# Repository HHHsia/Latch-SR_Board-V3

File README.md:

# Latch-SR_Board-V3  
含200單元Shift Register、400單元Latch(可選擇為200x2、80x5、40x10 Latch矩陣)  
輸入輸出各為20組20 pin FPC排線

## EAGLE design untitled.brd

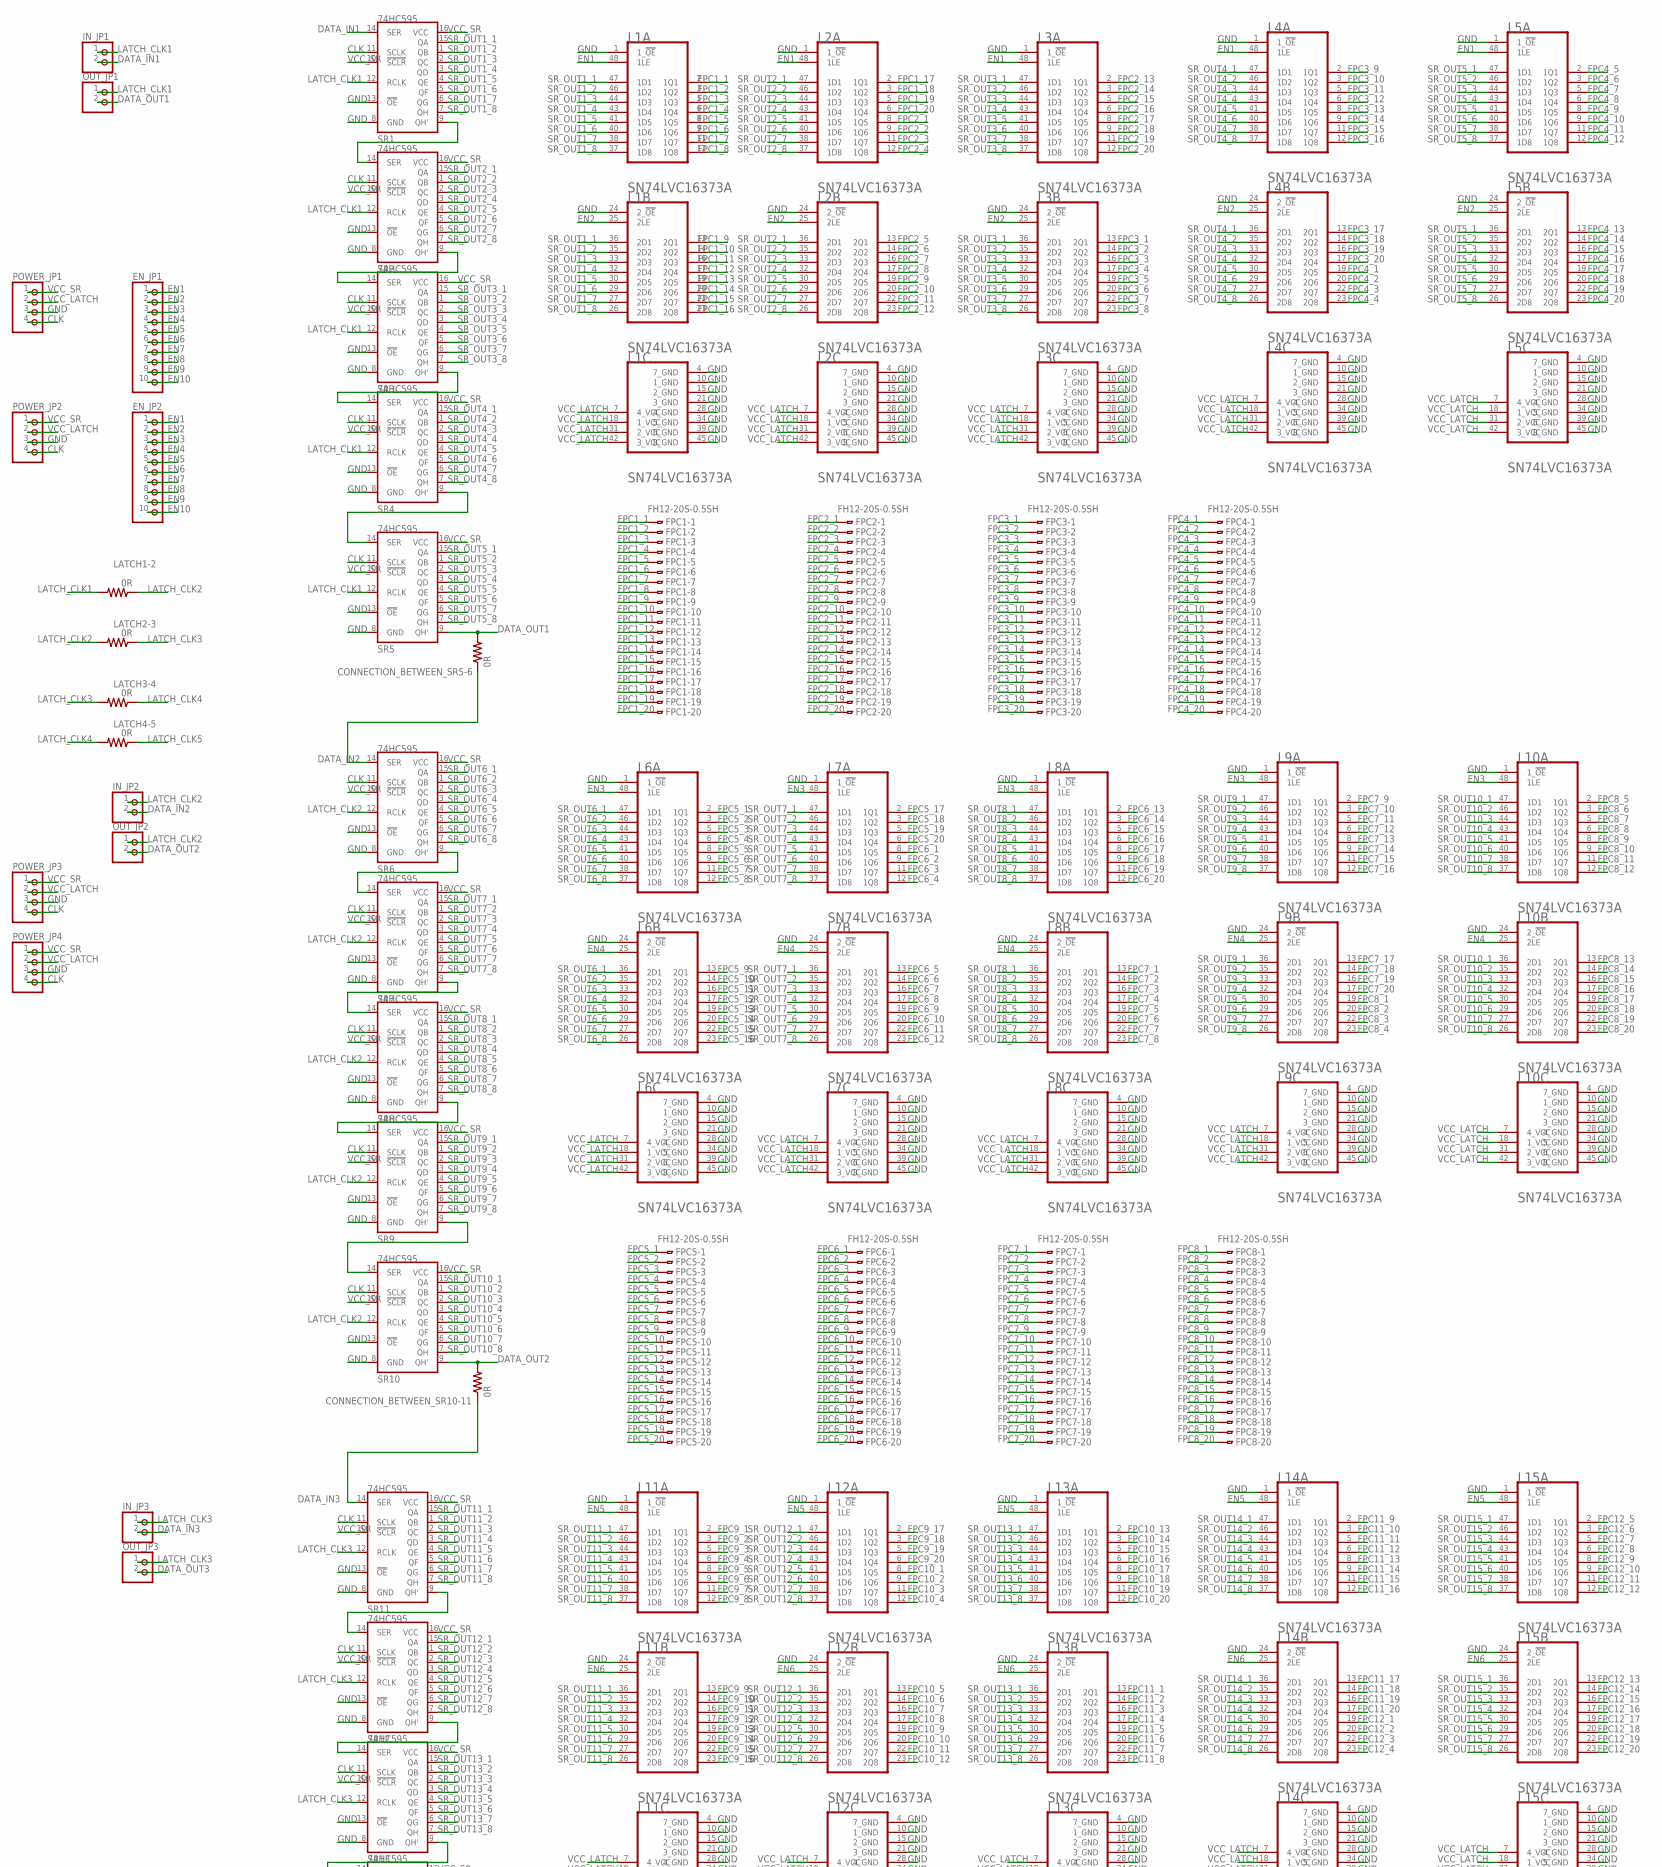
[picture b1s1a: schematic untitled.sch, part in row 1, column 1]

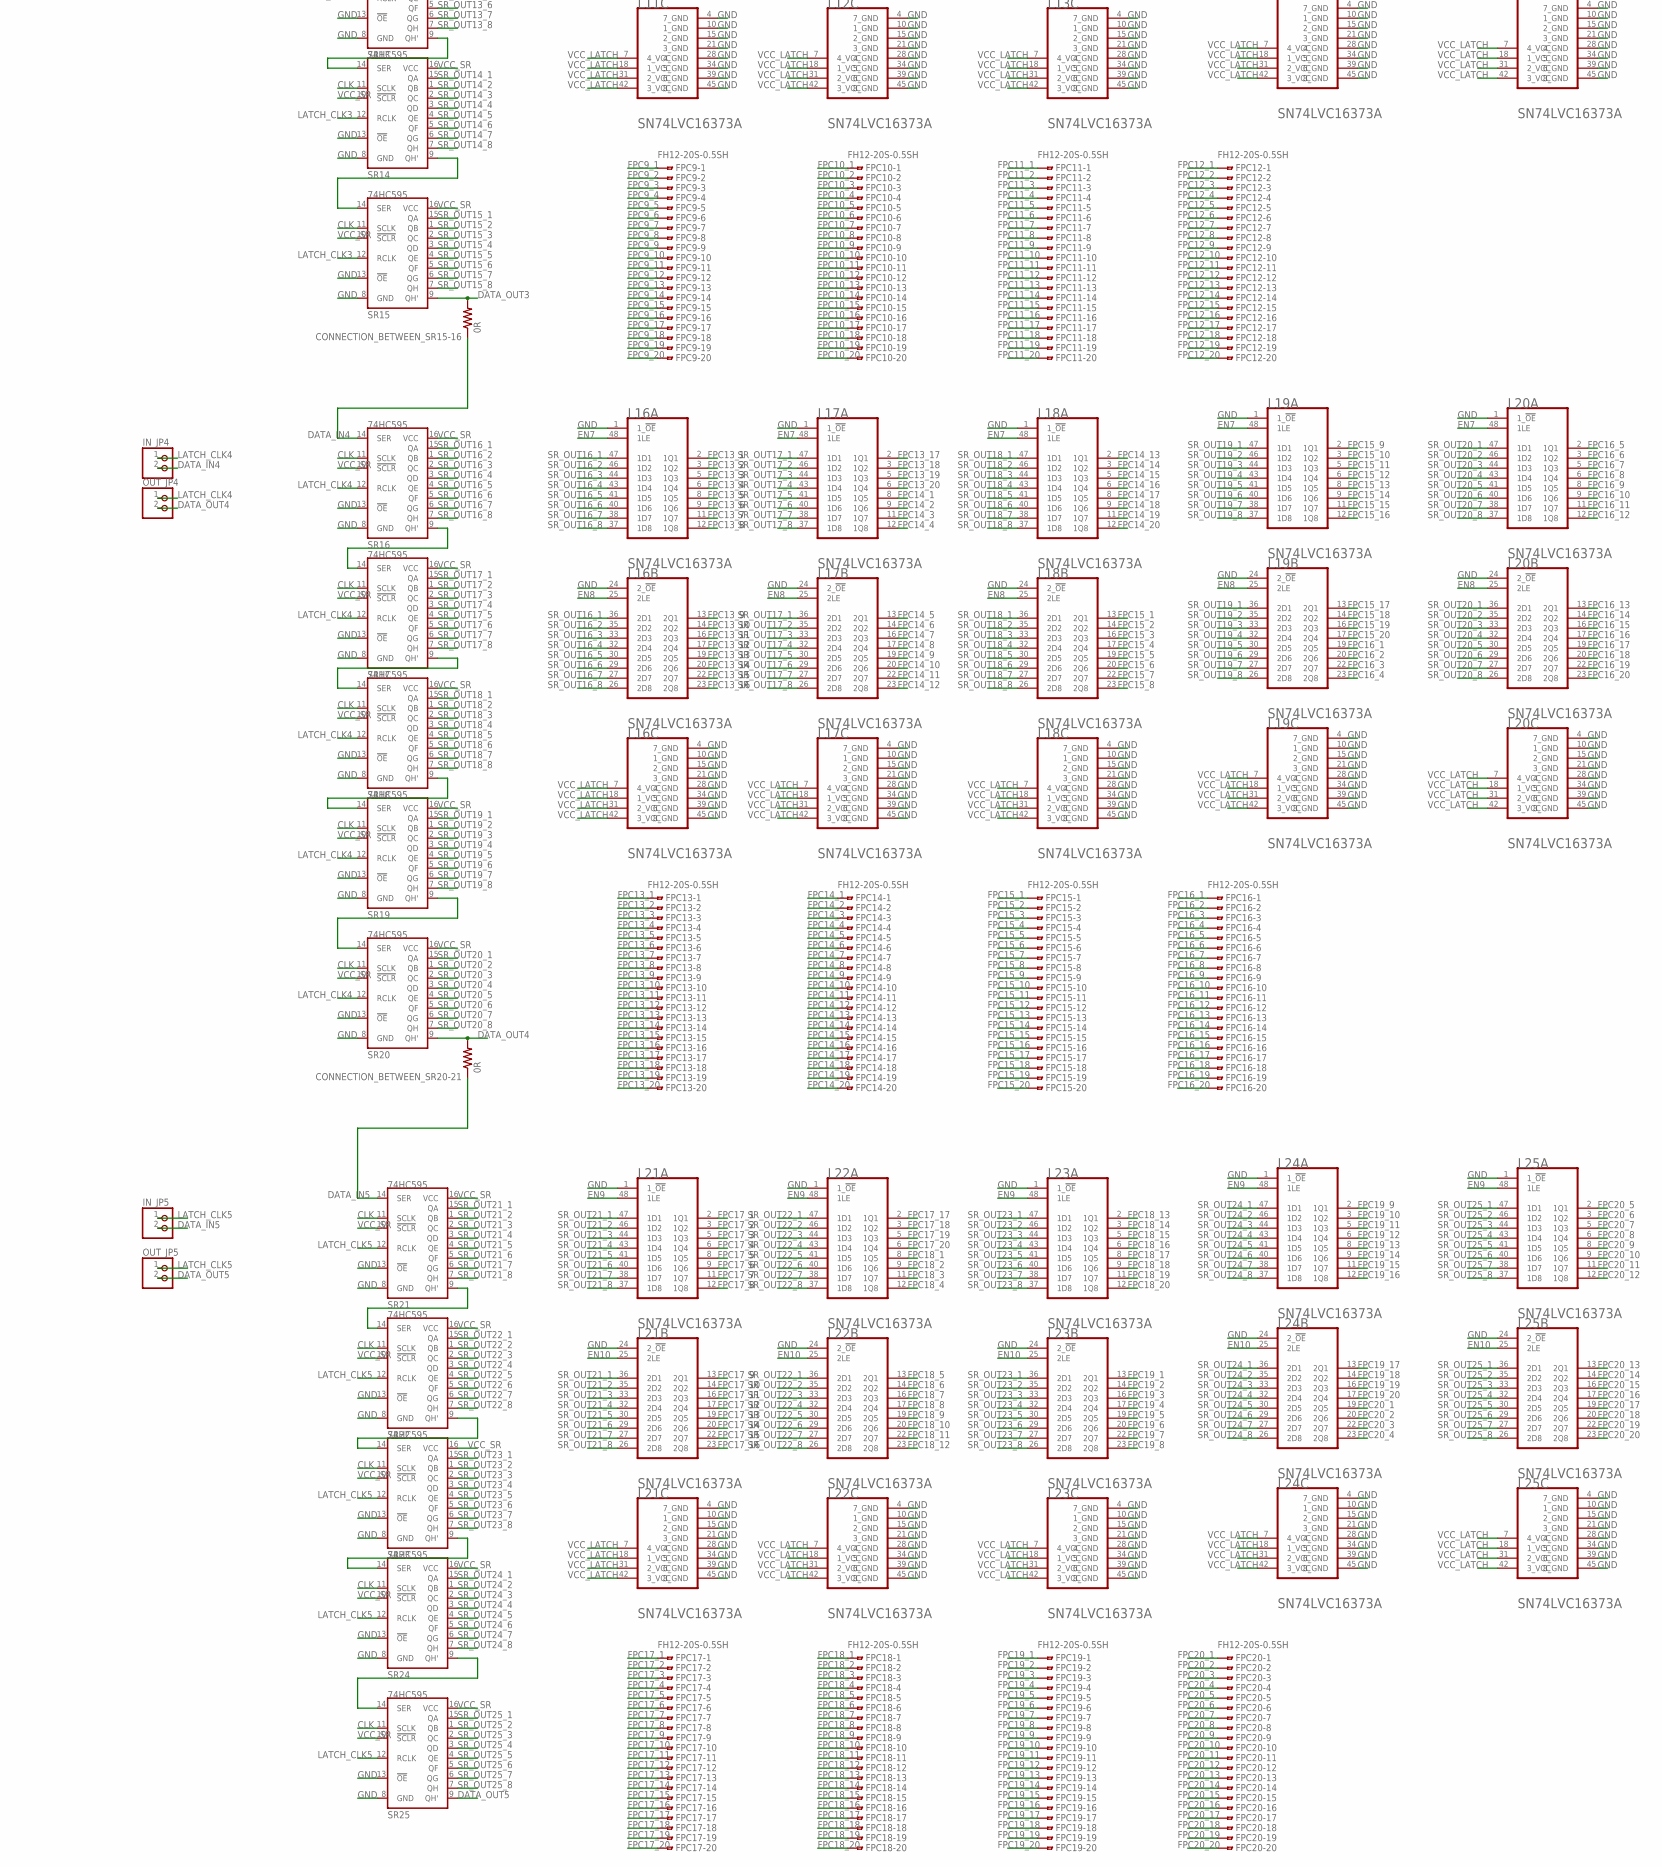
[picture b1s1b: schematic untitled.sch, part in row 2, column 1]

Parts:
CONNECTION_BETWEEN_SR5-6, CONNECTION_BETWEEN_SR10-11, CONNECTION_BETWEEN_SR15-16, CONNECTION_BETWEEN_SR20-21: 0R; M0805
EN_JP1, EN_JP2: PINHD-1X10; 1X10
FPC1, FPC2, FPC3, FPC4, FPC5, FPC6, FPC7, FPC8, FPC9, FPC10, FPC11, FPC12, FPC13, FPC14, FPC15, FPC16, FPC17, FPC18, FPC19, FPC20: FH12-20S-0.5SH
IN_JP1, IN_JP2, IN_JP3, IN_JP4, IN_JP5: PINHD-1X2; 1X02
L1, L2, L3, L4, L5, L6, L7, L8, L9, L10, L11, L12, L13, L14, L15, L16, L17, L18, L19, L20, L21, L22, L23, L24, L25: TEXAS_INSTRUMENTS_SN74LVC16373ATEXAS_INSTRUMENTS_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; TEXAS_INSTRUMENTS_SN74LVC16373A_2
LATCH1-2, LATCH2-3, LATCH3-4, LATCH4-5: 0R; M0805
OUT_JP1, OUT_JP2, OUT_JP3, OUT_JP4, OUT_JP5: PINHD-1X2; 1X02
POWER_JP1, POWER_JP2, POWER_JP3, POWER_JP4: PINHD-1X4; 1X04
SR1, SR2, SR3, SR4, SR5, SR6, SR7, SR8, SR9, SR10, SR11, SR12, SR13, SR14, SR15, SR16, SR17, SR18, SR19, SR20, SR21, SR22, SR23, SR24, SR25: 74HC595; SO16

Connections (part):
CLK: POWER_JP1.4, POWER_JP2.4, POWER_JP3.4, POWER_JP4.4, SR1.11 (SCLK), SR2.11 (SCLK), SR3.11 (SCLK), SR4.11 (SCLK), SR5.11 (SCLK), SR6.11 (SCLK), SR7.11 (SCLK), SR8.11 (SCLK), SR9.11 (SCLK), SR10.11 (SCLK), SR11.11 (SCLK), SR12.11 (SCLK), SR13.11 (SCLK), SR14.11 (SCLK), SR15.11 (SCLK), SR16.11 (SCLK), SR17.11 (SCLK), SR18.11 (SCLK), SR19.11 (SCLK), SR20.11 (SCLK), SR21.11 (SCLK), SR22.11 (SCLK), SR23.11 (SCLK), SR24.11 (SCLK), SR25.11 (SCLK)
DATA_IN1: IN_JP1.2, SR1.14 (SER)
DATA_IN2: CONNECTION_BETWEEN_SR5-6.1, IN_JP2.2, SR6.14 (SER)
DATA_IN3: CONNECTION_BETWEEN_SR10-11.1, IN_JP3.2, SR11.14 (SER)
DATA_IN4: CONNECTION_BETWEEN_SR15-16.1, IN_JP4.2, SR16.14 (SER)
DATA_IN5: CONNECTION_BETWEEN_SR20-21.1, IN_JP5.2, SR21.14 (SER)
DATA_OUT1: CONNECTION_BETWEEN_SR5-6.2, OUT_JP1.2, SR5.9 (QH')
DATA_OUT2: CONNECTION_BETWEEN_SR10-11.2, OUT_JP2.2, SR10.9 (QH')
DATA_OUT3: CONNECTION_BETWEEN_SR15-16.2, OUT_JP3.2, SR15.9 (QH')
DATA_OUT4: CONNECTION_BETWEEN_SR20-21.2, OUT_JP4.2, SR20.9 (QH')
DATA_OUT5: OUT_JP5.2, SR25.9 (QH')
EN1: EN_JP1.1, EN_JP2.1, L1.48 (1LE), L2.48 (1LE), L3.48 (1LE), L4.48 (1LE), L5.48 (1LE)
EN2: EN_JP1.2, EN_JP2.2, L1.25 (2LE), L2.25 (2LE), L3.25 (2LE), L4.25 (2LE), L5.25 (2LE)
EN3: EN_JP1.3, EN_JP2.3, L6.48 (1LE), L7.48 (1LE), L8.48 (1LE), L9.48 (1LE), L10.48 (1LE)
EN4: EN_JP1.4, EN_JP2.4, L6.25 (2LE), L7.25 (2LE), L8.25 (2LE), L9.25 (2LE), L10.25 (2LE)
EN5: EN_JP1.5, EN_JP2.5, L11.48 (1LE), L12.48 (1LE), L13.48 (1LE), L14.48 (1LE), L15.48 (1LE)
EN6: EN_JP1.6, EN_JP2.6, L11.25 (2LE), L12.25 (2LE), L13.25 (2LE), L14.25 (2LE), L15.25 (2LE)
EN7: EN_JP1.7, EN_JP2.7, L16.48 (1LE), L17.48 (1LE), L18.48 (1LE), L19.48 (1LE), L20.48 (1LE)
EN8: EN_JP1.8, EN_JP2.8, L16.25 (2LE), L17.25 (2LE), L18.25 (2LE), L19.25 (2LE), L20.25 (2LE)
EN9: EN_JP1.9, EN_JP2.9, L21.48 (1LE), L22.48 (1LE), L23.48 (1LE), L24.48 (1LE), L25.48 (1LE)
EN10: EN_JP1.10, EN_JP2.10, L21.25 (2LE), L22.25 (2LE), L23.25 (2LE), L24.25 (2LE), L25.25 (2LE)
FPC1_1: FPC1.1, L1.2 (1Q1)
FPC1_2: FPC1.2, L1.3 (1Q2)
FPC1_3: FPC1.3, L1.5 (1Q3)
FPC1_4: FPC1.4, L1.6 (1Q4)
FPC1_5: FPC1.5, L1.8 (1Q5)
FPC1_6: FPC1.6, L1.9 (1Q6)
FPC1_7: FPC1.7, L1.11 (1Q7)
FPC1_8: FPC1.8, L1.12 (1Q8)
FPC1_9: FPC1.9, L1.13 (2Q1)
FPC1_10: FPC1.10, L1.14 (2Q2)
FPC1_11: FPC1.11, L1.16 (2Q3)
FPC1_12: FPC1.12, L1.17 (2Q4)
FPC1_13: FPC1.13, L1.19 (2Q5)
FPC1_14: FPC1.14, L1.20 (2Q6)
FPC1_15: FPC1.15, L1.22 (2Q7)
FPC1_16: FPC1.16, L1.23 (2Q8)
FPC1_17: FPC1.17, L2.2 (1Q1)
FPC1_18: FPC1.18, L2.3 (1Q2)
FPC1_19: FPC1.19, L2.5 (1Q3)
FPC1_20: FPC1.20, L2.6 (1Q4)
FPC2_1: FPC2.1, L2.8 (1Q5)
FPC2_2: FPC2.2, L2.9 (1Q6)
FPC2_3: FPC2.3, L2.11 (1Q7)
FPC2_4: FPC2.4, L2.12 (1Q8)
FPC2_5: FPC2.5, L2.13 (2Q1)
FPC2_6: FPC2.6, L2.14 (2Q2)
FPC2_7: FPC2.7, L2.16 (2Q3)
FPC2_8: FPC2.8, L2.17 (2Q4)
FPC2_9: FPC2.9, L2.19 (2Q5)
FPC2_10: FPC2.10, L2.20 (2Q6)
FPC2_11: FPC2.11, L2.22 (2Q7)
FPC2_12: FPC2.12, L2.23 (2Q8)
FPC2_13: FPC2.13, L3.2 (1Q1)
FPC2_14: FPC2.14, L3.3 (1Q2)
FPC2_15: FPC2.15, L3.5 (1Q3)
FPC2_16: FPC2.16, L3.6 (1Q4)
FPC2_17: FPC2.17, L3.8 (1Q5)
FPC2_18: FPC2.18, L3.9 (1Q6)
FPC2_19: FPC2.19, L3.11 (1Q7)
FPC2_20: FPC2.20, L3.12 (1Q8)
FPC3_1: FPC3.1, L3.13 (2Q1)
FPC3_2: FPC3.2, L3.14 (2Q2)
FPC3_3: FPC3.3, L3.16 (2Q3)
FPC3_4: FPC3.4, L3.17 (2Q4)
FPC3_5: FPC3.5, L3.19 (2Q5)
FPC3_6: FPC3.6, L3.20 (2Q6)
FPC3_7: FPC3.7, L3.22 (2Q7)
FPC3_8: FPC3.8, L3.23 (2Q8)
FPC3_9: FPC3.9, L4.2 (1Q1)
FPC3_10: FPC3.10, L4.3 (1Q2)
FPC3_11: FPC3.11, L4.5 (1Q3)
FPC3_12: FPC3.12, L4.6 (1Q4)
FPC3_13: FPC3.13, L4.8 (1Q5)
FPC3_14: FPC3.14, L4.9 (1Q6)
FPC3_15: FPC3.15, L4.11 (1Q7)
FPC3_16: FPC3.16, L4.12 (1Q8)
FPC3_17: FPC3.17, L4.13 (2Q1)
FPC3_18: FPC3.18, L4.14 (2Q2)
FPC3_19: FPC3.19, L4.16 (2Q3)
FPC3_20: FPC3.20, L4.17 (2Q4)
FPC4_1: FPC4.1, L4.19 (2Q5)
FPC4_2: FPC4.2, L4.20 (2Q6)
FPC4_3: FPC4.3, L4.22 (2Q7)
FPC4_4: FPC4.4, L4.23 (2Q8)
FPC4_5: FPC4.5, L5.2 (1Q1)
FPC4_6: FPC4.6, L5.3 (1Q2)
FPC4_7: FPC4.7, L5.5 (1Q3)
FPC4_8: FPC4.8, L5.6 (1Q4)
FPC4_9: FPC4.9, L5.8 (1Q5)
FPC4_10: FPC4.10, L5.9 (1Q6)
FPC4_11: FPC4.11, L5.11 (1Q7)
FPC4_12: FPC4.12, L5.12 (1Q8)
FPC4_13: FPC4.13, L5.13 (2Q1)
FPC4_14: FPC4.14, L5.14 (2Q2)
FPC4_15: FPC4.15, L5.16 (2Q3)
FPC4_16: FPC4.16, L5.17 (2Q4)
FPC4_17: FPC4.17, L5.19 (2Q5)
FPC4_18: FPC4.18, L5.20 (2Q6)
FPC4_19: FPC4.19, L5.22 (2Q7)
FPC4_20: FPC4.20, L5.23 (2Q8)
FPC5_1: FPC5.1, L6.2 (1Q1)
FPC5_2: FPC5.2, L6.3 (1Q2)
FPC5_3: FPC5.3, L6.5 (1Q3)
FPC5_4: FPC5.4, L6.6 (1Q4)
FPC5_5: FPC5.5, L6.8 (1Q5)
FPC5_6: FPC5.6, L6.9 (1Q6)
FPC5_7: FPC5.7, L6.11 (1Q7)
FPC5_8: FPC5.8, L6.12 (1Q8)
FPC5_9: FPC5.9, L6.13 (2Q1)
FPC5_10: FPC5.10, L6.14 (2Q2)
FPC5_11: FPC5.11, L6.16 (2Q3)
FPC5_12: FPC5.12, L6.17 (2Q4)
FPC5_13: FPC5.13, L6.19 (2Q5)
FPC5_14: FPC5.14, L6.20 (2Q6)
FPC5_15: FPC5.15, L6.22 (2Q7)
FPC5_16: FPC5.16, L6.23 (2Q8)
FPC5_17: FPC5.17, L7.2 (1Q1)
FPC5_18: FPC5.18, L7.3 (1Q2)
FPC5_19: FPC5.19, L7.5 (1Q3)
FPC5_20: FPC5.20, L7.6 (1Q4)
FPC6_1: FPC6.1, L7.8 (1Q5)
FPC6_2: FPC6.2, L7.9 (1Q6)
FPC6_3: FPC6.3, L7.11 (1Q7)
FPC6_4: FPC6.4, L7.12 (1Q8)
FPC6_5: FPC6.5, L7.13 (2Q1)
FPC6_6: FPC6.6, L7.14 (2Q2)
FPC6_7: FPC6.7, L7.16 (2Q3)
FPC6_8: FPC6.8, L7.17 (2Q4)
FPC6_9: FPC6.9, L7.19 (2Q5)
FPC6_10: FPC6.10, L7.20 (2Q6)
FPC6_11: FPC6.11, L7.22 (2Q7)
FPC6_12: FPC6.12, L7.23 (2Q8)
FPC6_13: FPC6.13, L8.2 (1Q1)
FPC6_14: FPC6.14, L8.3 (1Q2)
FPC6_15: FPC6.15, L8.5 (1Q3)
FPC6_16: FPC6.16, L8.6 (1Q4)
FPC6_17: FPC6.17, L8.8 (1Q5)
FPC6_18: FPC6.18, L8.9 (1Q6)
FPC6_19: FPC6.19, L8.11 (1Q7)
FPC6_20: FPC6.20, L8.12 (1Q8)
FPC7_1: FPC7.1, L8.13 (2Q1)
FPC7_2: FPC7.2, L8.14 (2Q2)
FPC7_3: FPC7.3, L8.16 (2Q3)
FPC7_4: FPC7.4, L8.17 (2Q4)
FPC7_5: FPC7.5, L8.19 (2Q5)
FPC7_6: FPC7.6, L8.20 (2Q6)
FPC7_7: FPC7.7, L8.22 (2Q7)
FPC7_8: FPC7.8, L8.23 (2Q8)
FPC7_9: FPC7.9, L9.2 (1Q1)
FPC7_10: FPC7.10, L9.3 (1Q2)
FPC7_11: FPC7.11, L9.5 (1Q3)
FPC7_12: FPC7.12, L9.6 (1Q4)
FPC7_13: FPC7.13, L9.8 (1Q5)
FPC7_14: FPC7.14, L9.9 (1Q6)
FPC7_15: FPC7.15, L9.11 (1Q7)
FPC7_16: FPC7.16, L9.12 (1Q8)
FPC7_17: FPC7.17, L9.13 (2Q1)
FPC7_18: FPC7.18, L9.14 (2Q2)
FPC7_19: FPC7.19, L9.16 (2Q3)
FPC7_20: FPC7.20, L9.17 (2Q4)
FPC8_1: FPC8.1, L9.19 (2Q5)
FPC8_2: FPC8.2, L9.20 (2Q6)
FPC8_3: FPC8.3, L9.22 (2Q7)
FPC8_4: FPC8.4, L9.23 (2Q8)
FPC8_5: FPC8.5, L10.2 (1Q1)
FPC8_6: FPC8.6, L10.3 (1Q2)
FPC8_7: FPC8.7, L10.5 (1Q3)
FPC8_8: FPC8.8, L10.6 (1Q4)
FPC8_9: FPC8.9, L10.8 (1Q5)
FPC8_10: FPC8.10, L10.9 (1Q6)
FPC8_11: FPC8.11, L10.11 (1Q7)
FPC8_12: FPC8.12, L10.12 (1Q8)
FPC8_13: FPC8.13, L10.13 (2Q1)
FPC8_14: FPC8.14, L10.14 (2Q2)
FPC8_15: FPC8.15, L10.16 (2Q3)
FPC8_16: FPC8.16, L10.17 (2Q4)
FPC8_17: FPC8.17, L10.19 (2Q5)
FPC8_18: FPC8.18, L10.20 (2Q6)
FPC8_19: FPC8.19, L10.22 (2Q7)
FPC8_20: FPC8.20, L10.23 (2Q8)
FPC9_1: FPC9.1, L11.2 (1Q1)
FPC9_2: FPC9.2, L11.3 (1Q2)
FPC9_3: FPC9.3, L11.5 (1Q3)
FPC9_4: FPC9.4, L11.6 (1Q4)
FPC9_5: FPC9.5, L11.8 (1Q5)
FPC9_6: FPC9.6, L11.9 (1Q6)
FPC9_7: FPC9.7, L11.11 (1Q7)
FPC9_8: FPC9.8, L11.12 (1Q8)
FPC9_9: FPC9.9, L11.13 (2Q1)
FPC9_10: FPC9.10, L11.14 (2Q2)
FPC9_11: FPC9.11, L11.16 (2Q3)
FPC9_12: FPC9.12, L11.17 (2Q4)
FPC9_13: FPC9.13, L11.19 (2Q5)
FPC9_14: FPC9.14, L11.20 (2Q6)
FPC9_15: FPC9.15, L11.22 (2Q7)
FPC9_16: FPC9.16, L11.23 (2Q8)
FPC9_17: FPC9.17, L12.2 (1Q1)
FPC9_18: FPC9.18, L12.3 (1Q2)
FPC9_19: FPC9.19, L12.5 (1Q3)
FPC9_20: FPC9.20, L12.6 (1Q4)
FPC10_1: FPC10.1, L12.8 (1Q5)
FPC10_2: FPC10.2, L12.9 (1Q6)
FPC10_3: FPC10.3, L12.11 (1Q7)
FPC10_4: FPC10.4, L12.12 (1Q8)
FPC10_5: FPC10.5, L12.13 (2Q1)
FPC10_6: FPC10.6, L12.14 (2Q2)
FPC10_7: FPC10.7, L12.16 (2Q3)
FPC10_8: FPC10.8, L12.17 (2Q4)
FPC10_9: FPC10.9, L12.19 (2Q5)
FPC10_10: FPC10.10, L12.20 (2Q6)
FPC10_11: FPC10.11, L12.22 (2Q7)
FPC10_12: FPC10.12, L12.23 (2Q8)
FPC10_13: FPC10.13, L13.2 (1Q1)
FPC10_14: FPC10.14, L13.3 (1Q2)
FPC10_15: FPC10.15, L13.5 (1Q3)
FPC10_16: FPC10.16, L13.6 (1Q4)
FPC10_17: FPC10.17, L13.8 (1Q5)
FPC10_18: FPC10.18, L13.9 (1Q6)
FPC10_19: FPC10.19, L13.11 (1Q7)
FPC10_20: FPC10.20, L13.12 (1Q8)
FPC11_1: FPC11.1, L13.13 (2Q1)
FPC11_2: FPC11.2, L13.14 (2Q2)
FPC11_3: FPC11.3, L13.16 (2Q3)
FPC11_4: FPC11.4, L13.17 (2Q4)
FPC11_5: FPC11.5, L13.19 (2Q5)
FPC11_6: FPC11.6, L13.20 (2Q6)
FPC11_7: FPC11.7, L13.22 (2Q7)
FPC11_8: FPC11.8, L13.23 (2Q8)
FPC11_9: FPC11.9, L14.2 (1Q1)
FPC11_10: FPC11.10, L14.3 (1Q2)
FPC11_11: FPC11.11, L14.5 (1Q3)
FPC11_12: FPC11.12, L14.6 (1Q4)
FPC11_13: FPC11.13, L14.8 (1Q5)
FPC11_14: FPC11.14, L14.9 (1Q6)
FPC11_15: FPC11.15, L14.11 (1Q7)
FPC11_16: FPC11.16, L14.12 (1Q8)
FPC11_17: FPC11.17, L14.13 (2Q1)
FPC11_18: FPC11.18, L14.14 (2Q2)
FPC11_19: FPC11.19, L14.16 (2Q3)
FPC11_20: FPC11.20, L14.17 (2Q4)
FPC12_1: FPC12.1, L14.19 (2Q5)
FPC12_2: FPC12.2, L14.20 (2Q6)
FPC12_3: FPC12.3, L14.22 (2Q7)
FPC12_4: FPC12.4, L14.23 (2Q8)
FPC12_5: FPC12.5, L15.2 (1Q1)
FPC12_6: FPC12.6, L15.3 (1Q2)
FPC12_7: FPC12.7, L15.5 (1Q3)
FPC12_8: FPC12.8, L15.6 (1Q4)
FPC12_9: FPC12.9, L15.8 (1Q5)
FPC12_10: FPC12.10, L15.9 (1Q6)
FPC12_11: FPC12.11, L15.11 (1Q7)
FPC12_12: FPC12.12, L15.12 (1Q8)
FPC12_13: FPC12.13, L15.13 (2Q1)
FPC12_14: FPC12.14, L15.14 (2Q2)
FPC12_15: FPC12.15, L15.16 (2Q3)
FPC12_16: FPC12.16, L15.17 (2Q4)
FPC12_17: FPC12.17, L15.19 (2Q5)
FPC12_18: FPC12.18, L15.20 (2Q6)
FPC12_19: FPC12.19, L15.22 (2Q7)
FPC12_20: FPC12.20, L15.23 (2Q8)
FPC13_1: FPC13.1, L16.2 (1Q1)
FPC13_2: FPC13.2, L16.3 (1Q2)
FPC13_3: FPC13.3, L16.5 (1Q3)
FPC13_4: FPC13.4, L16.6 (1Q4)
FPC13_5: FPC13.5, L16.8 (1Q5)
FPC13_6: FPC13.6, L16.9 (1Q6)
FPC13_7: FPC13.7, L16.11 (1Q7)
FPC13_8: FPC13.8, L16.12 (1Q8)
FPC13_9: FPC13.9, L16.13 (2Q1)
FPC13_10: FPC13.10, L16.14 (2Q2)
FPC13_11: FPC13.11, L16.16 (2Q3)
FPC13_12: FPC13.12, L16.17 (2Q4)
FPC13_13: FPC13.13, L16.19 (2Q5)
FPC13_14: FPC13.14, L16.20 (2Q6)
FPC13_15: FPC13.15, L16.22 (2Q7)
FPC13_16: FPC13.16, L16.23 (2Q8)
FPC13_17: FPC13.17, L17.2 (1Q1)
FPC13_18: FPC13.18, L17.3 (1Q2)
FPC13_19: FPC13.19, L17.5 (1Q3)
FPC13_20: FPC13.20, L17.6 (1Q4)
FPC14_1: FPC14.1, L17.8 (1Q5)
FPC14_2: FPC14.2, L17.9 (1Q6)
FPC14_3: FPC14.3, L17.11 (1Q7)
FPC14_4: FPC14.4, L17.12 (1Q8)
FPC14_5: FPC14.5, L17.13 (2Q1)
FPC14_6: FPC14.6, L17.14 (2Q2)
FPC14_7: FPC14.7, L17.16 (2Q3)
FPC14_8: FPC14.8, L17.17 (2Q4)
FPC14_9: FPC14.9, L17.19 (2Q5)
FPC14_10: FPC14.10, L17.20 (2Q6)
FPC14_11: FPC14.11, L17.22 (2Q7)
FPC14_12: FPC14.12, L17.23 (2Q8)
FPC14_13: FPC14.13, L18.2 (1Q1)
FPC14_14: FPC14.14, L18.3 (1Q2)
FPC14_15: FPC14.15, L18.5 (1Q3)
FPC14_16: FPC14.16, L18.6 (1Q4)
FPC14_17: FPC14.17, L18.8 (1Q5)
FPC14_18: FPC14.18, L18.9 (1Q6)
FPC14_19: FPC14.19, L18.11 (1Q7)
FPC14_20: FPC14.20, L18.12 (1Q8)
FPC15_1: FPC15.1, L18.13 (2Q1)
FPC15_2: FPC15.2, L18.14 (2Q2)
FPC15_3: FPC15.3, L18.16 (2Q3)
FPC15_4: FPC15.4, L18.17 (2Q4)
FPC15_5: FPC15.5, L18.19 (2Q5)
FPC15_6: FPC15.6, L18.20 (2Q6)
FPC15_7: FPC15.7, L18.22 (2Q7)
FPC15_8: FPC15.8, L18.23 (2Q8)
FPC15_9: FPC15.9, L19.2 (1Q1)
FPC15_10: FPC15.10, L19.3 (1Q2)
FPC15_11: FPC15.11, L19.5 (1Q3)
FPC15_12: FPC15.12, L19.6 (1Q4)
FPC15_13: FPC15.13, L19.8 (1Q5)
FPC15_14: FPC15.14, L19.9 (1Q6)
FPC15_15: FPC15.15, L19.11 (1Q7)
FPC15_16: FPC15.16, L19.12 (1Q8)
FPC15_17: FPC15.17, L19.13 (2Q1)
FPC15_18: FPC15.18, L19.14 (2Q2)
FPC15_19: FPC15.19, L19.16 (2Q3)
FPC15_20: FPC15.20, L19.17 (2Q4)
FPC16_1: FPC16.1, L19.19 (2Q5)
FPC16_2: FPC16.2, L19.20 (2Q6)
FPC16_3: FPC16.3, L19.22 (2Q7)
FPC16_4: FPC16.4, L19.23 (2Q8)
FPC16_5: FPC16.5, L20.2 (1Q1)
FPC16_6: FPC16.6, L20.3 (1Q2)
FPC16_7: FPC16.7, L20.5 (1Q3)
FPC16_8: FPC16.8, L20.6 (1Q4)
FPC16_9: FPC16.9, L20.8 (1Q5)
FPC16_10: FPC16.10, L20.9 (1Q6)
FPC16_11: FPC16.11, L20.11 (1Q7)
FPC16_12: FPC16.12, L20.12 (1Q8)
FPC16_13: FPC16.13, L20.13 (2Q1)
FPC16_14: FPC16.14, L20.14 (2Q2)
FPC16_15: FPC16.15, L20.16 (2Q3)
FPC16_16: FPC16.16, L20.17 (2Q4)
FPC16_17: FPC16.17, L20.19 (2Q5)
FPC16_18: FPC16.18, L20.20 (2Q6)
FPC16_19: FPC16.19, L20.22 (2Q7)
FPC16_20: FPC16.20, L20.23 (2Q8)
FPC17_1: FPC17.1, L21.2 (1Q1)
FPC17_2: FPC17.2, L21.3 (1Q2)
FPC17_3: FPC17.3, L21.5 (1Q3)
FPC17_4: FPC17.4, L21.6 (1Q4)
FPC17_5: FPC17.5, L21.8 (1Q5)
FPC17_6: FPC17.6, L21.9 (1Q6)
FPC17_7: FPC17.7, L21.11 (1Q7)
FPC17_8: FPC17.8, L21.12 (1Q8)
FPC17_9: FPC17.9, L21.13 (2Q1)
FPC17_10: FPC17.10, L21.14 (2Q2)
FPC17_11: FPC17.11, L21.16 (2Q3)
FPC17_12: FPC17.12, L21.17 (2Q4)
FPC17_13: FPC17.13, L21.19 (2Q5)
FPC17_14: FPC17.14, L21.20 (2Q6)
FPC17_15: FPC17.15, L21.22 (2Q7)
FPC17_16: FPC17.16, L21.23 (2Q8)
FPC17_17: FPC17.17, L22.2 (1Q1)
FPC17_18: FPC17.18, L22.3 (1Q2)
FPC17_19: FPC17.19, L22.5 (1Q3)
FPC17_20: FPC17.20, L22.6 (1Q4)
FPC18_1: FPC18.1, L22.8 (1Q5)
FPC18_2: FPC18.2, L22.9 (1Q6)
FPC18_3: FPC18.3, L22.11 (1Q7)
FPC18_4: FPC18.4, L22.12 (1Q8)
FPC18_5: FPC18.5, L22.13 (2Q1)
FPC18_6: FPC18.6, L22.14 (2Q2)
FPC18_7: FPC18.7, L22.16 (2Q3)
FPC18_8: FPC18.8, L22.17 (2Q4)
FPC18_9: FPC18.9, L22.19 (2Q5)
FPC18_10: FPC18.10, L22.20 (2Q6)
FPC18_11: FPC18.11, L22.22 (2Q7)
FPC18_12: FPC18.12, L22.23 (2Q8)
FPC18_13: FPC18.13, L23.2 (1Q1)
FPC18_14: FPC18.14, L23.3 (1Q2)
FPC18_15: FPC18.15, L23.5 (1Q3)
FPC18_16: FPC18.16, L23.6 (1Q4)
FPC18_17: FPC18.17, L23.8 (1Q5)
FPC18_18: FPC18.18, L23.9 (1Q6)
FPC18_19: FPC18.19, L23.11 (1Q7)
FPC18_20: FPC18.20, L23.12 (1Q8)
FPC19_1: FPC19.1, L23.13 (2Q1)
FPC19_2: FPC19.2, L23.14 (2Q2)
FPC19_3: FPC19.3, L23.16 (2Q3)
FPC19_4: FPC19.4, L23.17 (2Q4)
FPC19_5: FPC19.5, L23.19 (2Q5)
FPC19_6: FPC19.6, L23.20 (2Q6)
FPC19_7: FPC19.7, L23.22 (2Q7)
FPC19_8: FPC19.8, L23.23 (2Q8)
FPC19_9: FPC19.9, L24.2 (1Q1)
FPC19_10: FPC19.10, L24.3 (1Q2)
FPC19_11: FPC19.11, L24.5 (1Q3)
FPC19_12: FPC19.12, L24.6 (1Q4)
FPC19_13: FPC19.13, L24.8 (1Q5)
FPC19_14: FPC19.14, L24.9 (1Q6)
FPC19_15: FPC19.15, L24.11 (1Q7)
FPC19_16: FPC19.16, L24.12 (1Q8)
FPC19_17: FPC19.17, L24.13 (2Q1)
FPC19_18: FPC19.18, L24.14 (2Q2)
FPC19_19: FPC19.19, L24.16 (2Q3)
FPC19_20: FPC19.20, L24.17 (2Q4)
FPC20_1: FPC20.1, L24.19 (2Q5)
FPC20_2: FPC20.2, L24.20 (2Q6)
FPC20_3: FPC20.3, L24.22 (2Q7)
FPC20_4: FPC20.4, L24.23 (2Q8)
FPC20_5: FPC20.5, L25.2 (1Q1)
FPC20_6: FPC20.6, L25.3 (1Q2)
FPC20_7: FPC20.7, L25.5 (1Q3)
FPC20_8: FPC20.8, L25.6 (1Q4)
FPC20_9: FPC20.9, L25.8 (1Q5)
FPC20_10: FPC20.10, L25.9 (1Q6)
FPC20_11: FPC20.11, L25.11 (1Q7)
FPC20_12: FPC20.12, L25.12 (1Q8)
FPC20_13: FPC20.13, L25.13 (2Q1)
FPC20_14: FPC20.14, L25.14 (2Q2)
FPC20_15: FPC20.15, L25.16 (2Q3)
FPC20_16: FPC20.16, L25.17 (2Q4)
FPC20_17: FPC20.17, L25.19 (2Q5)
FPC20_18: FPC20.18, L25.20 (2Q6)
FPC20_19: FPC20.19, L25.22 (2Q7)
FPC20_20: FPC20.20, L25.23 (2Q8)
GND: L1.1 (1_!OE!), L1.4 (7_GND), L1.10 (1_GND), L1.15 (2_GND), L1.21 (3_GND), L1.24 (2_!OE!), L1.28 (4_GND), L1.34 (5_GND), L1.39 (6_GND), L1.45 (8_GND), L2.1 (1_!OE!), L2.4 (7_GND), L2.10 (1_GND), L2.15 (2_GND), L2.21 (3_GND), L2.24 (2_!OE!), L2.28 (4_GND), L2.34 (5_GND), L2.39 (6_GND), L2.45 (8_GND), L3.1 (1_!OE!), L3.4 (7_GND), L3.10 (1_GND), L3.15 (2_GND), L3.21 (3_GND), L3.24 (2_!OE!), L3.28 (4_GND), L3.34 (5_GND), L3.39 (6_GND), L3.45 (8_GND), L4.1 (1_!OE!), L4.4 (7_GND), L4.10 (1_GND), L4.15 (2_GND), L4.21 (3_GND), L4.24 (2_!OE!), L4.28 (4_GND), L4.34 (5_GND), L4.39 (6_GND), L4.45 (8_GND), L5.1 (1_!OE!), L5.4 (7_GND), L5.10 (1_GND), L5.15 (2_GND), L5.21 (3_GND), L5.24 (2_!OE!), L5.28 (4_GND), L5.34 (5_GND), L5.39 (6_GND), L5.45 (8_GND), L6.1 (1_!OE!), L6.4 (7_GND), L6.10 (1_GND), L6.15 (2_GND), L6.21 (3_GND), L6.24 (2_!OE!), L6.28 (4_GND), L6.34 (5_GND), L6.39 (6_GND), L6.45 (8_GND), L7.1 (1_!OE!), L7.4 (7_GND), L7.10 (1_GND), L7.15 (2_GND), L7.21 (3_GND), L7.24 (2_!OE!), L7.28 (4_GND), L7.34 (5_GND), L7.39 (6_GND), L7.45 (8_GND), L8.1 (1_!OE!), L8.4 (7_GND), L8.10 (1_GND), L8.15 (2_GND), L8.21 (3_GND), L8.24 (2_!OE!), L8.28 (4_GND), L8.34 (5_GND), L8.39 (6_GND), L8.45 (8_GND), L9.1 (1_!OE!), L9.4 (7_GND), L9.10 (1_GND)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
LATCH_CLK1: IN_JP1.1, LATCH1-2.2, OUT_JP1.1, SR1.12 (RCLK), SR2.12 (RCLK), SR3.12 (RCLK), SR4.12 (RCLK), SR5.12 (RCLK)
LATCH_CLK2: IN_JP2.1, LATCH1-2.1, LATCH2-3.2, OUT_JP2.1, SR6.12 (RCLK), SR7.12 (RCLK), SR8.12 (RCLK), SR9.12 (RCLK), SR10.12 (RCLK)
LATCH_CLK3: IN_JP3.1, LATCH2-3.1, LATCH3-4.2, OUT_JP3.1, SR11.12 (RCLK), SR12.12 (RCLK), SR13.12 (RCLK), SR14.12 (RCLK), SR15.12 (RCLK)
LATCH_CLK4: IN_JP4.1, LATCH3-4.1, LATCH4-5.2, OUT_JP4.1, SR16.12 (RCLK), SR17.12 (RCLK), SR18.12 (RCLK), SR19.12 (RCLK), SR20.12 (RCLK)
LATCH_CLK5: IN_JP5.1, LATCH4-5.1, OUT_JP5.1, SR21.12 (RCLK), SR22.12 (RCLK), SR23.12 (RCLK), SR24.12 (RCLK), SR25.12 (RCLK)
unnamed: SR1.9 (QH'), SR2.14 (SER)
unnamed: SR4.9 (QH'), SR5.14 (SER)
unnamed: SR6.9 (QH'), SR7.14 (SER)
unnamed: SR7.9 (QH'), SR8.14 (SER)
unnamed: SR8.9 (QH'), SR9.14 (SER)
unnamed: SR9.9 (QH'), SR10.14 (SER)
unnamed: SR11.9 (QH'), SR12.14 (SER)
unnamed: SR2.9 (QH'), SR3.14 (SER)
unnamed: SR12.9 (QH'), SR13.14 (SER)
unnamed: SR13.9 (QH'), SR14.14 (SER)
unnamed: SR14.9 (QH'), SR15.14 (SER)
unnamed: SR16.9 (QH'), SR17.14 (SER)
unnamed: SR17.9 (QH'), SR18.14 (SER)
unnamed: SR3.9 (QH'), SR4.14 (SER)
unnamed: SR18.9 (QH'), SR19.14 (SER)
unnamed: SR19.9 (QH'), SR20.14 (SER)
unnamed: SR21.9 (QH'), SR22.14 (SER)
unnamed: SR22.9 (QH'), SR23.14 (SER)
unnamed: SR23.9 (QH'), SR24.14 (SER)
unnamed: SR24.9 (QH'), SR25.14 (SER)
SR_OUT1_1: L1.36 (2D1), L1.47 (1D1), SR1.15 (QA)
SR_OUT1_2: L1.35 (2D2), L1.46 (1D2), SR1.1 (QB)
SR_OUT1_3: L1.33 (2D3), L1.44 (1D3), SR1.2 (QC)
SR_OUT1_4: L1.32 (2D4), L1.43 (1D4), SR1.3 (QD)
SR_OUT1_5: L1.30 (2D5), L1.41 (1D5), SR1.4 (QE)
SR_OUT1_6: L1.29 (2D6), L1.40 (1D6), SR1.5 (QF)
SR_OUT1_7: L1.27 (2D7), L1.38 (1D7), SR1.6 (QG)
SR_OUT1_8: L1.26 (2D8), L1.37 (1D8), SR1.7 (QH)
SR_OUT2_1: L2.36 (2D1), L2.47 (1D1), SR2.15 (QA)
SR_OUT2_2: L2.35 (2D2), L2.46 (1D2), SR2.1 (QB)
SR_OUT2_3: L2.33 (2D3), L2.44 (1D3), SR2.2 (QC)
SR_OUT2_4: L2.32 (2D4), L2.43 (1D4), SR2.3 (QD)
SR_OUT2_5: L2.30 (2D5), L2.41 (1D5), SR2.4 (QE)
SR_OUT2_6: L2.29 (2D6), L2.40 (1D6), SR2.5 (QF)
SR_OUT2_7: L2.27 (2D7), L2.38 (1D7), SR2.6 (QG)
SR_OUT2_8: L2.26 (2D8), L2.37 (1D8), SR2.7 (QH)
SR_OUT3_1: L3.36 (2D1), L3.47 (1D1), SR3.15 (QA)
SR_OUT3_2: L3.35 (2D2), L3.46 (1D2), SR3.1 (QB)
SR_OUT3_3: L3.33 (2D3), L3.44 (1D3), SR3.2 (QC)
SR_OUT3_4: L3.32 (2D4), L3.43 (1D4), SR3.3 (QD)
SR_OUT3_5: L3.30 (2D5), L3.41 (1D5), SR3.4 (QE)
SR_OUT3_6: L3.29 (2D6), L3.40 (1D6), SR3.5 (QF)
SR_OUT3_7: L3.27 (2D7), L3.38 (1D7), SR3.6 (QG)
SR_OUT3_8: L3.26 (2D8), L3.37 (1D8), SR3.7 (QH)
SR_OUT4_1: L4.36 (2D1), L4.47 (1D1), SR4.15 (QA)
SR_OUT4_2: L4.35 (2D2), L4.46 (1D2), SR4.1 (QB)
SR_OUT4_3: L4.33 (2D3), L4.44 (1D3), SR4.2 (QC)
SR_OUT4_4: L4.32 (2D4), L4.43 (1D4), SR4.3 (QD)
SR_OUT4_5: L4.30 (2D5), L4.41 (1D5), SR4.4 (QE)
SR_OUT4_6: L4.29 (2D6), L4.40 (1D6), SR4.5 (QF)
SR_OUT4_7: L4.27 (2D7), L4.38 (1D7), SR4.6 (QG)
SR_OUT4_8: L4.26 (2D8), L4.37 (1D8), SR4.7 (QH)
SR_OUT5_1: L5.36 (2D1), L5.47 (1D1), SR5.15 (QA)
SR_OUT5_2: L5.35 (2D2), L5.46 (1D2), SR5.1 (QB)
SR_OUT5_3: L5.33 (2D3), L5.44 (1D3), SR5.2 (QC)
SR_OUT5_4: L5.32 (2D4), L5.43 (1D4), SR5.3 (QD)
SR_OUT5_5: L5.30 (2D5), L5.41 (1D5), SR5.4 (QE)
SR_OUT5_6: L5.29 (2D6), L5.40 (1D6), SR5.5 (QF)
SR_OUT5_7: L5.27 (2D7), L5.38 (1D7), SR5.6 (QG)
SR_OUT5_8: L5.26 (2D8), L5.37 (1D8), SR5.7 (QH)
SR_OUT6_1: L6.36 (2D1), L6.47 (1D1), SR6.15 (QA)
SR_OUT6_2: L6.35 (2D2), L6.46 (1D2), SR6.1 (QB)
SR_OUT6_3: L6.33 (2D3), L6.44 (1D3), SR6.2 (QC)
SR_OUT6_4: L6.32 (2D4), L6.43 (1D4), SR6.3 (QD)
SR_OUT6_5: L6.30 (2D5), L6.41 (1D5), SR6.4 (QE)
SR_OUT6_6: L6.29 (2D6), L6.40 (1D6), SR6.5 (QF)
SR_OUT6_7: L6.27 (2D7), L6.38 (1D7), SR6.6 (QG)
SR_OUT6_8: L6.26 (2D8), L6.37 (1D8), SR6.7 (QH)
SR_OUT7_1: L7.36 (2D1), L7.47 (1D1), SR7.15 (QA)
SR_OUT7_2: L7.35 (2D2), L7.46 (1D2), SR7.1 (QB)
SR_OUT7_3: L7.33 (2D3), L7.44 (1D3), SR7.2 (QC)
SR_OUT7_4: L7.32 (2D4), L7.43 (1D4), SR7.3 (QD)
SR_OUT7_5: L7.30 (2D5), L7.41 (1D5), SR7.4 (QE)
SR_OUT7_6: L7.29 (2D6), L7.40 (1D6), SR7.5 (QF)
SR_OUT7_7: L7.27 (2D7), L7.38 (1D7), SR7.6 (QG)
SR_OUT7_8: L7.26 (2D8), L7.37 (1D8), SR7.7 (QH)
SR_OUT8_1: L8.36 (2D1), L8.47 (1D1), SR8.15 (QA)
SR_OUT8_2: L8.35 (2D2), L8.46 (1D2), SR8.1 (QB)
SR_OUT8_3: L8.33 (2D3), L8.44 (1D3), SR8.2 (QC)
SR_OUT8_4: L8.32 (2D4), L8.43 (1D4), SR8.3 (QD)
SR_OUT8_5: L8.30 (2D5), L8.41 (1D5), SR8.4 (QE)
SR_OUT8_6: L8.29 (2D6), L8.40 (1D6), SR8.5 (QF)
SR_OUT8_7: L8.27 (2D7), L8.38 (1D7), SR8.6 (QG)
SR_OUT8_8: L8.26 (2D8), L8.37 (1D8), SR8.7 (QH)
SR_OUT9_1: L9.36 (2D1), L9.47 (1D1), SR9.15 (QA)
SR_OUT9_2: L9.35 (2D2), L9.46 (1D2), SR9.1 (QB)
SR_OUT9_3: L9.33 (2D3), L9.44 (1D3), SR9.2 (QC)
SR_OUT9_4: L9.32 (2D4), L9.43 (1D4), SR9.3 (QD)
SR_OUT9_5: L9.30 (2D5), L9.41 (1D5), SR9.4 (QE)
SR_OUT9_6: L9.29 (2D6), L9.40 (1D6), SR9.5 (QF)
SR_OUT9_7: L9.27 (2D7), L9.38 (1D7), SR9.6 (QG)
SR_OUT9_8: L9.26 (2D8), L9.37 (1D8), SR9.7 (QH)
SR_OUT10_1: L10.36 (2D1), L10.47 (1D1), SR10.15 (QA)
SR_OUT10_2: L10.35 (2D2), L10.46 (1D2), SR10.1 (QB)
SR_OUT10_3: L10.33 (2D3), L10.44 (1D3), SR10.2 (QC)
SR_OUT10_4: L10.32 (2D4), L10.43 (1D4), SR10.3 (QD)
SR_OUT10_5: L10.30 (2D5), L10.41 (1D5), SR10.4 (QE)
SR_OUT10_6: L10.29 (2D6), L10.40 (1D6), SR10.5 (QF)
SR_OUT10_7: L10.27 (2D7), L10.38 (1D7), SR10.6 (QG)
SR_OUT10_8: L10.26 (2D8), L10.37 (1D8), SR10.7 (QH)
SR_OUT11_1: L11.36 (2D1), L11.47 (1D1), SR11.15 (QA)
SR_OUT11_2: L11.35 (2D2), L11.46 (1D2), SR11.1 (QB)
SR_OUT11_3: L11.33 (2D3), L11.44 (1D3), SR11.2 (QC)
SR_OUT11_4: L11.32 (2D4), L11.43 (1D4), SR11.3 (QD)
SR_OUT11_5: L11.30 (2D5), L11.41 (1D5), SR11.4 (QE)
SR_OUT11_6: L11.29 (2D6), L11.40 (1D6), SR11.5 (QF)
SR_OUT11_7: L11.27 (2D7), L11.38 (1D7), SR11.6 (QG)
SR_OUT11_8: L11.26 (2D8), L11.37 (1D8), SR11.7 (QH)
SR_OUT12_1: L12.36 (2D1), L12.47 (1D1), SR12.15 (QA)
SR_OUT12_2: L12.35 (2D2), L12.46 (1D2), SR12.1 (QB)
SR_OUT12_3: L12.33 (2D3), L12.44 (1D3), SR12.2 (QC)
SR_OUT12_4: L12.32 (2D4), L12.43 (1D4), SR12.3 (QD)
SR_OUT12_5: L12.30 (2D5), L12.41 (1D5), SR12.4 (QE)
SR_OUT12_6: L12.29 (2D6), L12.40 (1D6), SR12.5 (QF)
SR_OUT12_7: L12.27 (2D7), L12.38 (1D7), SR12.6 (QG)
SR_OUT12_8: L12.26 (2D8), L12.37 (1D8), SR12.7 (QH)
SR_OUT13_1: L13.36 (2D1), L13.47 (1D1), SR13.15 (QA)
SR_OUT13_2: L13.35 (2D2), L13.46 (1D2), SR13.1 (QB)
SR_OUT13_3: L13.33 (2D3), L13.44 (1D3), SR13.2 (QC)
SR_OUT13_4: L13.32 (2D4), L13.43 (1D4), SR13.3 (QD)
SR_OUT13_5: L13.30 (2D5), L13.41 (1D5), SR13.4 (QE)
SR_OUT13_6: L13.29 (2D6), L13.40 (1D6), SR13.5 (QF)
SR_OUT13_7: L13.27 (2D7), L13.38 (1D7), SR13.6 (QG)
SR_OUT13_8: L13.26 (2D8), L13.37 (1D8), SR13.7 (QH)
SR_OUT14_1: L14.36 (2D1), L14.47 (1D1), SR14.15 (QA)
SR_OUT14_2: L14.35 (2D2), L14.46 (1D2), SR14.1 (QB)
SR_OUT14_3: L14.33 (2D3), L14.44 (1D3), SR14.2 (QC)
SR_OUT14_4: L14.32 (2D4), L14.43 (1D4), SR14.3 (QD)
SR_OUT14_5: L14.30 (2D5), L14.41 (1D5), SR14.4 (QE)
SR_OUT14_6: L14.29 (2D6), L14.40 (1D6), SR14.5 (QF)
SR_OUT14_7: L14.27 (2D7), L14.38 (1D7), SR14.6 (QG)
SR_OUT14_8: L14.26 (2D8), L14.37 (1D8), SR14.7 (QH)
SR_OUT15_1: L15.36 (2D1), L15.47 (1D1), SR15.15 (QA)
SR_OUT15_2: L15.35 (2D2), L15.46 (1D2), SR15.1 (QB)
SR_OUT15_3: L15.33 (2D3), L15.44 (1D3), SR15.2 (QC)
SR_OUT15_4: L15.32 (2D4), L15.43 (1D4), SR15.3 (QD)
SR_OUT15_5: L15.30 (2D5), L15.41 (1D5), SR15.4 (QE)
SR_OUT15_6: L15.29 (2D6), L15.40 (1D6), SR15.5 (QF)
SR_OUT15_7: L15.27 (2D7), L15.38 (1D7), SR15.6 (QG)
SR_OUT15_8: L15.26 (2D8), L15.37 (1D8), SR15.7 (QH)
SR_OUT16_1: L16.36 (2D1), L16.47 (1D1), SR16.15 (QA)
SR_OUT16_2: L16.35 (2D2), L16.46 (1D2), SR16.1 (QB)
SR_OUT16_3: L16.33 (2D3), L16.44 (1D3), SR16.2 (QC)
SR_OUT16_4: L16.32 (2D4), L16.43 (1D4), SR16.3 (QD)
SR_OUT16_5: L16.30 (2D5), L16.41 (1D5), SR16.4 (QE)
SR_OUT16_6: L16.29 (2D6), L16.40 (1D6), SR16.5 (QF)
SR_OUT16_7: L16.27 (2D7), L16.38 (1D7), SR16.6 (QG)
SR_OUT16_8: L16.26 (2D8), L16.37 (1D8), SR16.7 (QH)
SR_OUT17_1: L17.36 (2D1), L17.47 (1D1), SR17.15 (QA)
SR_OUT17_2: L17.35 (2D2), L17.46 (1D2), SR17.1 (QB)
SR_OUT17_3: L17.33 (2D3), L17.44 (1D3), SR17.2 (QC)
SR_OUT17_4: L17.32 (2D4), L17.43 (1D4), SR17.3 (QD)
SR_OUT17_5: L17.30 (2D5), L17.41 (1D5), SR17.4 (QE)
SR_OUT17_6: L17.29 (2D6), L17.40 (1D6), SR17.5 (QF)
SR_OUT17_7: L17.27 (2D7), L17.38 (1D7), SR17.6 (QG)
SR_OUT17_8: L17.26 (2D8), L17.37 (1D8), SR17.7 (QH)
SR_OUT18_1: L18.36 (2D1), L18.47 (1D1), SR18.15 (QA)
SR_OUT18_2: L18.35 (2D2), L18.46 (1D2), SR18.1 (QB)
SR_OUT18_3: L18.33 (2D3), L18.44 (1D3), SR18.2 (QC)
SR_OUT18_4: L18.32 (2D4), L18.43 (1D4), SR18.3 (QD)
SR_OUT18_5: L18.30 (2D5), L18.41 (1D5), SR18.4 (QE)
SR_OUT18_6: L18.29 (2D6), L18.40 (1D6), SR18.5 (QF)
SR_OUT18_7: L18.27 (2D7), L18.38 (1D7), SR18.6 (QG)
SR_OUT18_8: L18.26 (2D8), L18.37 (1D8), SR18.7 (QH)
SR_OUT19_1: L19.36 (2D1), L19.47 (1D1), SR19.15 (QA)
SR_OUT19_2: L19.35 (2D2), L19.46 (1D2), SR19.1 (QB)
SR_OUT19_3: L19.33 (2D3), L19.44 (1D3), SR19.2 (QC)
SR_OUT19_4: L19.32 (2D4), L19.43 (1D4), SR19.3 (QD)
SR_OUT19_5: L19.30 (2D5), L19.41 (1D5), SR19.4 (QE)
SR_OUT19_6: L19.29 (2D6), L19.40 (1D6), SR19.5 (QF)
SR_OUT19_7: L19.27 (2D7), L19.38 (1D7), SR19.6 (QG)
SR_OUT19_8: L19.26 (2D8), L19.37 (1D8), SR19.7 (QH)
SR_OUT20_1: L20.36 (2D1), L20.47 (1D1), SR20.15 (QA)
SR_OUT20_2: L20.35 (2D2), L20.46 (1D2), SR20.1 (QB)
SR_OUT20_3: L20.33 (2D3), L20.44 (1D3), SR20.2 (QC)
SR_OUT20_4: L20.32 (2D4), L20.43 (1D4), SR20.3 (QD)
SR_OUT20_5: L20.30 (2D5), L20.41 (1D5), SR20.4 (QE)
SR_OUT20_6: L20.29 (2D6), L20.40 (1D6), SR20.5 (QF)
SR_OUT20_7: L20.27 (2D7), L20.38 (1D7), SR20.6 (QG)
SR_OUT20_8: L20.26 (2D8), L20.37 (1D8), SR20.7 (QH)
SR_OUT21_1: L21.36 (2D1), L21.47 (1D1), SR21.15 (QA)
SR_OUT21_2: L21.35 (2D2), L21.46 (1D2), SR21.1 (QB)
SR_OUT21_3: L21.33 (2D3), L21.44 (1D3), SR21.2 (QC)
SR_OUT21_4: L21.32 (2D4), L21.43 (1D4), SR21.3 (QD)
SR_OUT21_5: L21.30 (2D5), L21.41 (1D5), SR21.4 (QE)
SR_OUT21_6: L21.29 (2D6), L21.40 (1D6), SR21.5 (QF)
SR_OUT21_7: L21.27 (2D7), L21.38 (1D7), SR21.6 (QG)
SR_OUT21_8: L21.26 (2D8), L21.37 (1D8), SR21.7 (QH)
SR_OUT22_1: L22.36 (2D1), L22.47 (1D1), SR22.15 (QA)
SR_OUT22_2: L22.35 (2D2), L22.46 (1D2), SR22.1 (QB)
SR_OUT22_3: L22.33 (2D3), L22.44 (1D3), SR22.2 (QC)
SR_OUT22_4: L22.32 (2D4), L22.43 (1D4), SR22.3 (QD)
SR_OUT22_5: L22.30 (2D5), L22.41 (1D5), SR22.4 (QE)
SR_OUT22_6: L22.29 (2D6), L22.40 (1D6), SR22.5 (QF)
SR_OUT22_7: L22.27 (2D7), L22.38 (1D7), SR22.6 (QG)
SR_OUT22_8: L22.26 (2D8), L22.37 (1D8), SR22.7 (QH)
SR_OUT23_1: L23.36 (2D1), L23.47 (1D1), SR23.15 (QA)
SR_OUT23_2: L23.35 (2D2), L23.46 (1D2), SR23.1 (QB)
SR_OUT23_3: L23.33 (2D3), L23.44 (1D3), SR23.2 (QC)
SR_OUT23_4: L23.32 (2D4), L23.43 (1D4), SR23.3 (QD)
SR_OUT23_5: L23.30 (2D5), L23.41 (1D5), SR23.4 (QE)
SR_OUT23_6: L23.29 (2D6), L23.40 (1D6), SR23.5 (QF)
SR_OUT23_7: L23.27 (2D7), L23.38 (1D7), SR23.6 (QG)
SR_OUT23_8: L23.26 (2D8), L23.37 (1D8), SR23.7 (QH)
SR_OUT24_1: L24.36 (2D1), L24.47 (1D1), SR24.15 (QA)
SR_OUT24_2: L24.35 (2D2), L24.46 (1D2), SR24.1 (QB)
SR_OUT24_3: L24.33 (2D3), L24.44 (1D3), SR24.2 (QC)
SR_OUT24_4: L24.32 (2D4), L24.43 (1D4), SR24.3 (QD)
SR_OUT24_5: L24.30 (2D5), L24.41 (1D5), SR24.4 (QE)
SR_OUT24_6: L24.29 (2D6), L24.40 (1D6), SR24.5 (QF)
SR_OUT24_7: L24.27 (2D7), L24.38 (1D7), SR24.6 (QG)
SR_OUT24_8: L24.26 (2D8), L24.37 (1D8), SR24.7 (QH)
SR_OUT25_1: L25.36 (2D1), L25.47 (1D1), SR25.15 (QA)
SR_OUT25_2: L25.35 (2D2), L25.46 (1D2), SR25.1 (QB)
SR_OUT25_3: L25.33 (2D3), L25.44 (1D3), SR25.2 (QC)
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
